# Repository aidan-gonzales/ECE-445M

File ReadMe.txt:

These files accompany "Introduction to Embedded Systems using the MSPM0+" 
Jonathan W. Valvano, ISBN: 978-1466468863, copyright (c) 2026

Most of the folders contain CCS projects. Folders that begin with the name RTOS_ are ECE445M lab starter projects

These folders do not contain CCS projects
  The documentation folder contains html descriptions created by Doxygen
  The datasheets folder contains data sheets for components used in this curriculum
  The RTOS_Labs_common folder contains shared files for the RTOS labs  
  The inc folder contains general shared files. 
  The SensorBoard_v8 folder contains design files for the sensor board
  The MotorBoard_v7 folder contains design files for the motor board

TExaSdisplay is a Windows application that implements a serial terminal, oscilloscope and logic analyzer.

Built 1/10/2026

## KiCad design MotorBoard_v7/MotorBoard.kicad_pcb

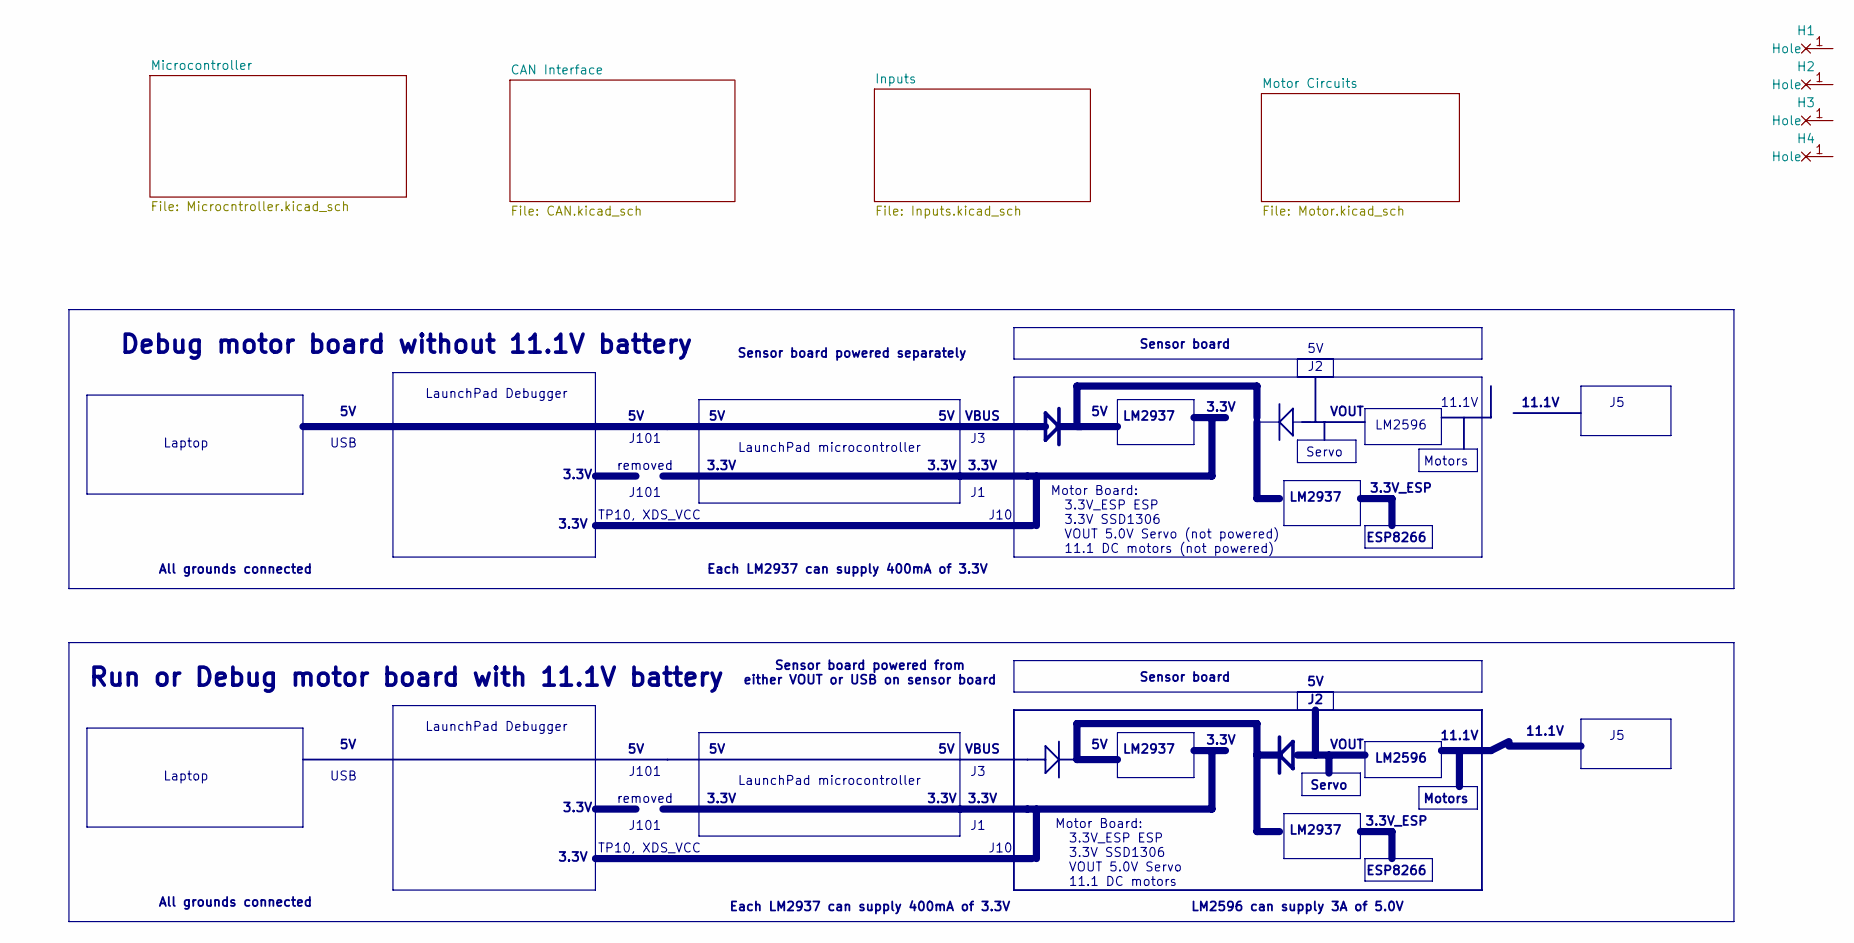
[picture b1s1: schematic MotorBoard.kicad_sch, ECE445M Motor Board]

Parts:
H1, H2, H3, H4: MountingHole_4_40

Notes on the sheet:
3.3V
Each LM2937 can supply 400mA of 3.3V
Motors
LaunchPad Debugger
3.3V_ESP
USB
Laptop
VOUT
Debug motor board without 11.1V battery
Sensor board
Motor Board: 3.3V_ESP ESP 3.3V SSD1306 VOUT 5.0V Servo 11.1 DC motors
Servo
LM2596 can supply 3A of 5.0V
VBUS
All grounds connected
ESP8266
LM2937
J10
LaunchPad microcontroller
removed
11.1V
Sensor board powered separately
LM2596
TP10, XDS_VCC
Run or Debug motor board with 11.1V battery
J101
Sensor board powered from either VOUT or USB on sensor board
Motor Board: 3.3V_ESP ESP 3.3V SSD1306 VOUT 5.0V Servo (not powered) 11.1 DC motors (not powered)

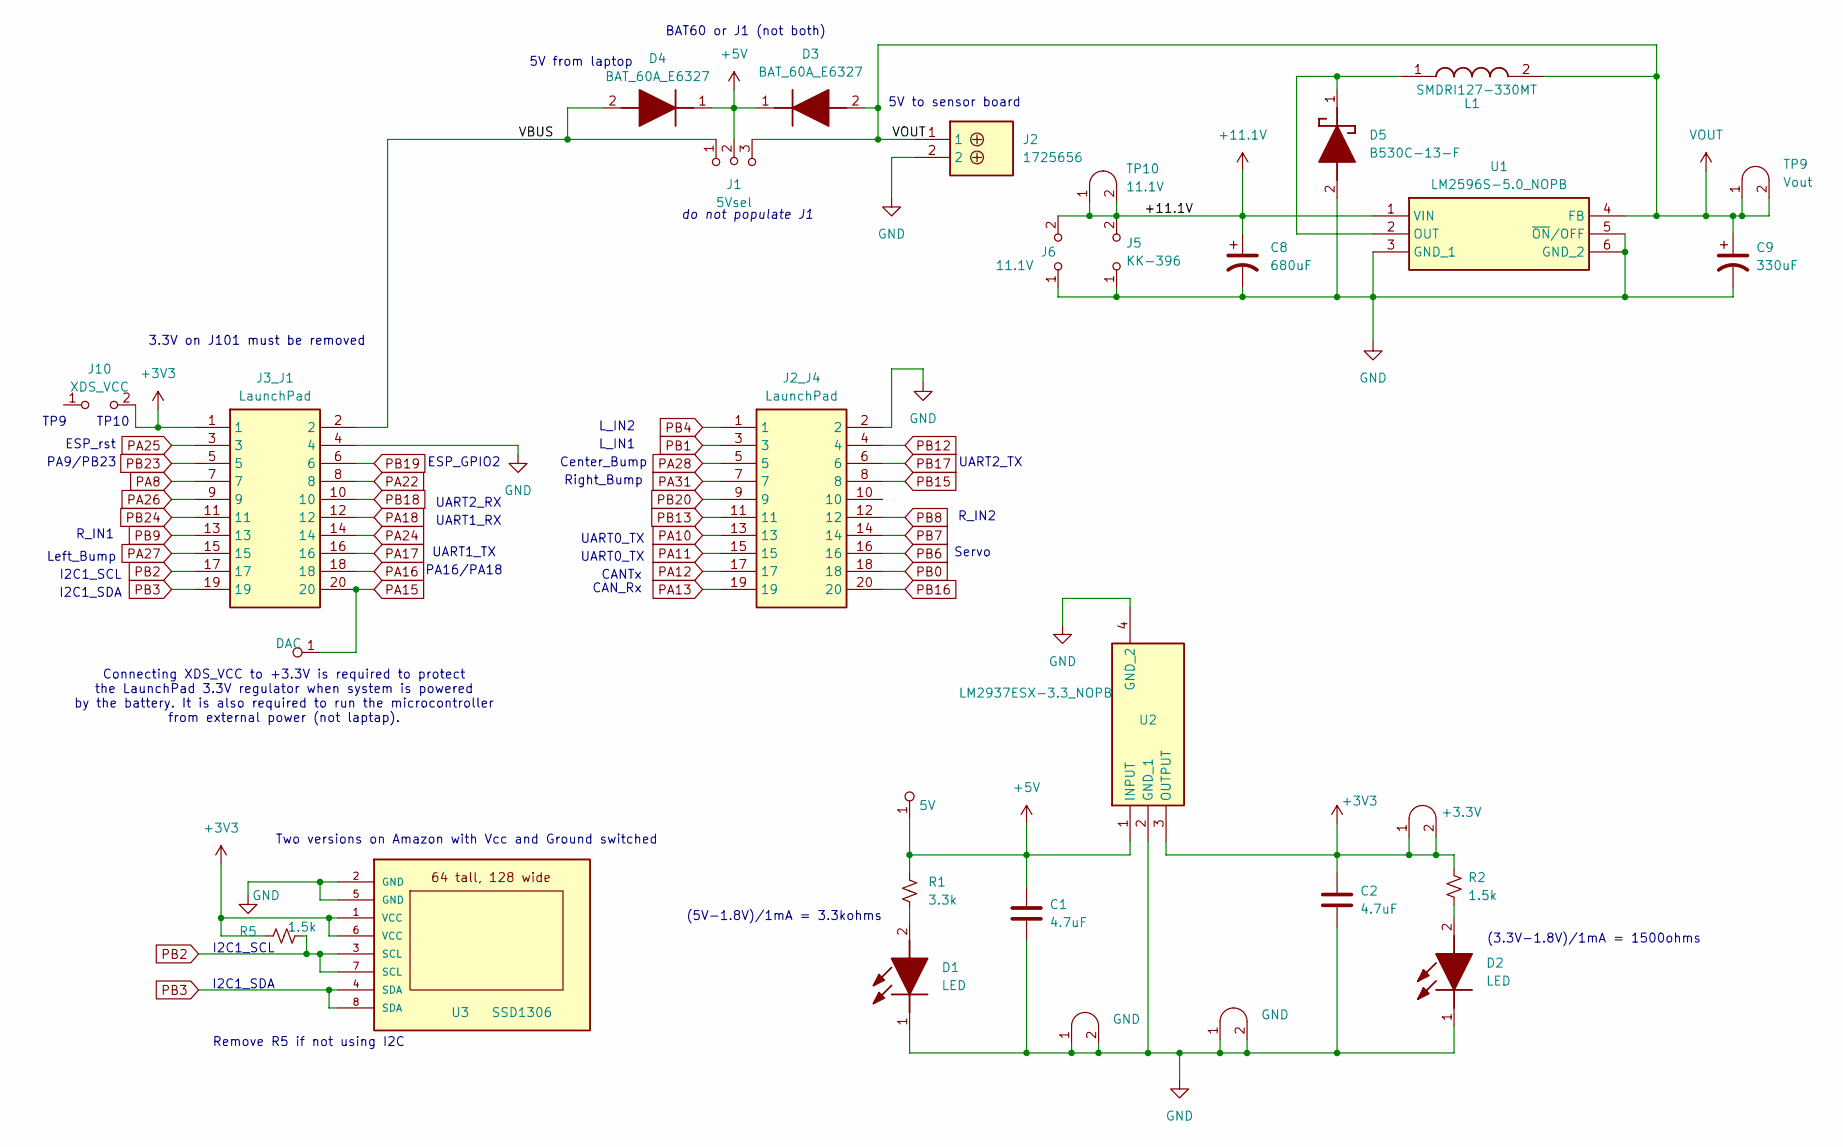
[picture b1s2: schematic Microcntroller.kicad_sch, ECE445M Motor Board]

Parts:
C1, C2: 4.7uF; C_0805_2012Metric; LCSC C5186689
C8: 680uF; CP_Elec_10x10.5; LCSC C2980172
C9: 330uF; CP_Elec_10x10.5; LCSC C5155335
D1, D2: LED; APT1608CGCK; Mouser Part Number 604-APTD1608LSECKJ3F
D3, D4: BAT_60A_E6327; SOD2513X110N; Mouser Part Number 726-BAT60AE6327
D5: B530C-13-F; DO-214AB; Mouser Part Number 621-B530C-13-F
J1: 5Vsel; PinHeader_1x03_P2.54mm_Vertical
J2: 1725656; Mouser Part Number 651-1725656
J2_J4, J3_J1: LaunchPad; Mouser Part Number 855-M20-8761042P
J5: KK-396; Molex_KK-396_A-41792-0002_1x02_P3.96mm_Horizontal
J6: 11.1V; PinHeader_1x02_P2.54mm_Vertical
J10: XDS_VCC; PinHeader_1x02_P2.54mm_Vertical
L1: SMDRI127-330MT; INDPM120120X800N; Mouser Part Number 851-CDRH127LDNP330MC
R1: 3.3k; R_0603_1608Metric; LCSC C340542
R2, R5: 1.5k; R_0603_1608Metric; LCSC C340542
TP1: DAC; Testpoint_1x1; Digikey 36-5000-ND, 36-5001-ND, 36-5002-ND , 36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
TP2: 5V; Testpoint_1x1; Digikey 36-5000-ND, 36-5001-ND, 36-5002-ND , 36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
TP3: +3.3V; Testpoint_1x02_P2.54mm; Digikey 36-5000-ND, 36-5001-ND, 36-5002-ND , 36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
TP9: Vout; Testpoint_1x02_P2.54mm
TP10: 11.1V; Testpoint_1x02_P2.54mm
TP11, TP16: GND; Testpoint_1x02_P2.54mm
U1: LM2596S-5.0_NOPB; KTT0005B; Mouser Part Number 926-LM2596S-5.0/NOPB
U2: LM2937ESX-3.3_NOPB; SOT230P700X180-4N; Mouser Part Number 926-LM2937IMP3.3NOPB
U3: SSD1306

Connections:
+3V3: C2.1, J3_J1.1, J10.2 (B), R2.1, R5.1, TP3.1 (A), TP3.2 (B), U2.3 (OUTPUT), U3.1 (VCC), U3.6 (VCC); also elsewhere on the board
+5V: C1.1, D3.1 (K), D4.1 (K), J1.2 (B), R1.1, TP2.1 (A), U2.1 (INPUT); also elsewhere on the board
+11.1V: C8.1, J5.2 (B), J6.2 (B), TP10.1 (A), TP10.2 (B), U1.1 (VIN); also elsewhere on the board
/Microcontroller/VBUS: D4.2 (A), J1.1 (A), J3_J1.2
GND: C1.2, C2.2, C8.2, C9.2, D1.1 (K), D2.1 (K), D5.2 (A), J2.2, J2_J4.2, J3_J1.4, J5.1 (A), J6.1 (A), TP11.1 (A), TP11.2 (B), TP16.1 (A), TP16.2 (B), U1.3 (GND_1), U1.5 (~ON/OFF), U1.6 (GND_2), U2.2 (GND_1), U2.4 (GND_2), U3.2 (GND), U3.5 (GND); also elsewhere on the board
unnamed: D1.2 (A), R1.2
unnamed: D2.2 (A), R2.2
unnamed: D5.1 (K), L1.1, U1.2 (OUT)
PA8: J3_J1.7
PA10: J2_J4.13
PA11: J2_J4.15
PA12: J2_J4.17; also elsewhere on the board
PA13: J2_J4.19; also elsewhere on the board
PA15: J3_J1.20, TP1.1 (A)
PA16: J3_J1.18
PA17: J3_J1.16
PA18: J3_J1.12
PA22: J3_J1.8
PA24: J3_J1.14
PA25: J3_J1.3; also elsewhere on the board
PA26: J3_J1.9
PA27: J3_J1.15; also elsewhere on the board
PA28: J2_J4.5; also elsewhere on the board
PA31: J2_J4.7; also elsewhere on the board
PB0: J2_J4.18
PB1: J2_J4.3; also elsewhere on the board
PB2: J3_J1.17, R5.2, U3.3 (SCL), U3.7 (SCL)
PB3: J3_J1.19, U3.4 (SDA), U3.8 (SDA)
PB4: J2_J4.1; also elsewhere on the board
PB6: J2_J4.16; also elsewhere on the board
PB7: J2_J4.14
PB8: J2_J4.12; also elsewhere on the board
PB9: J3_J1.13; also elsewhere on the board
PB12: J2_J4.4
PB13: J2_J4.11
PB15: J2_J4.8
PB16: J2_J4.20
PB17: J2_J4.6; also elsewhere on the board
PB18: J3_J1.10; also elsewhere on the board
PB19: J3_J1.6; also elsewhere on the board
PB20: J2_J4.9
PB23: J3_J1.5
PB24: J3_J1.11
VOUT: C9.1, D3.2 (A), J1.3 (C), J2.1, L1.2, TP9.1 (A), TP9.2 (B), U1.4 (FB); also elsewhere on the board

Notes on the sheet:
TP10
UART0_TX
UART1_RX
(5V-1.8V)/1mA = 3.3kohms
(3.3V-1.8V)/1mA = 1500ohms
Left_Bump
5V from laptop
ESP_GPIO2
UART2_RX
CANTx
UART1_TX
Right_Bump
3.3V on J101 must be removed
L_IN1
Servo
Center_Bump
I2C1_SDA
PA16/PA18
BAT60 or J1 (not both)
Remove R5 if not using I2C
TP9
do not populate J1
UART2_TX
R_IN2
PA9/PB23
I2C1_SCL
5V to sensor board
R_IN1
CAN_Rx
ESP_rst
Two versions on Amazon with Vcc and Ground switched
Connecting XDS_VCC to +3.3V is required to protect the LaunchPad 3.3V regulator when system is powered by the battery. It is also required to run the microcontroller from external power (not laptap).
L_IN2

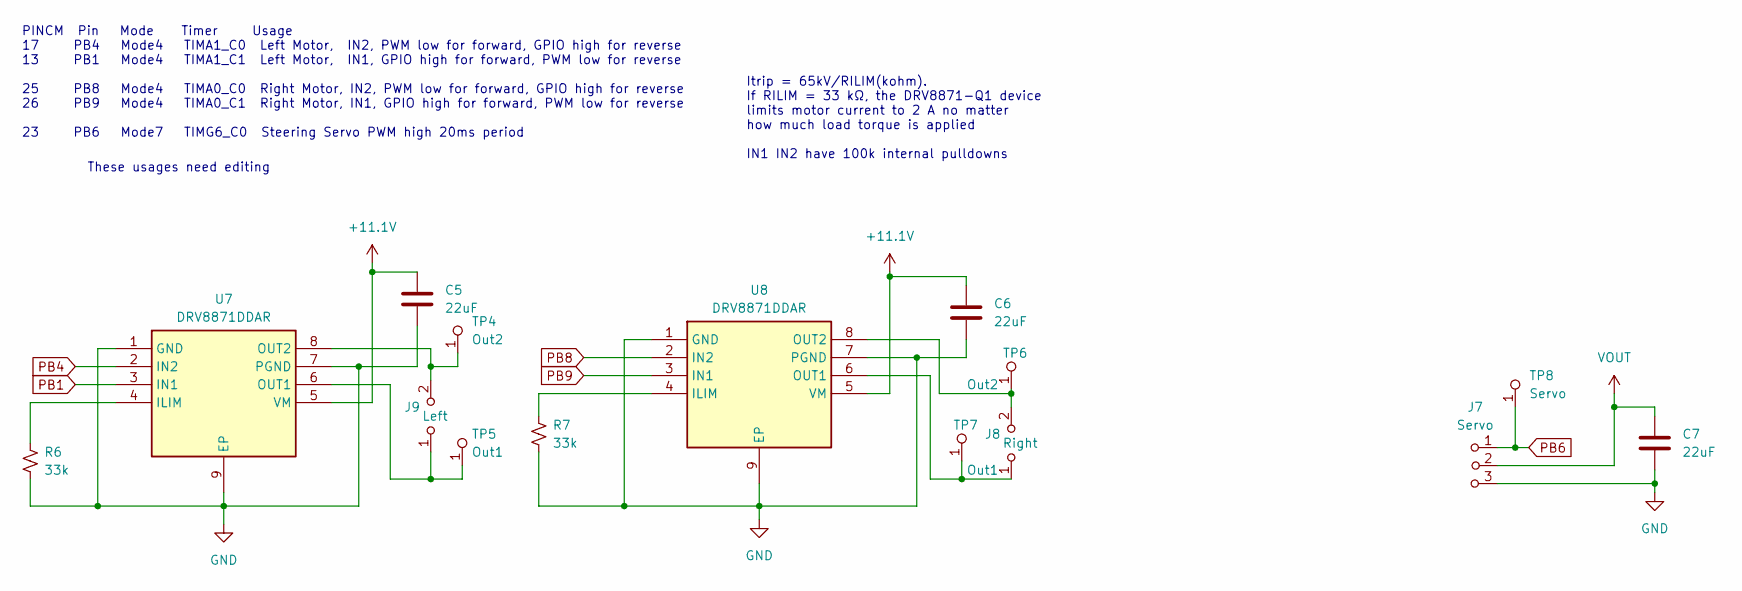
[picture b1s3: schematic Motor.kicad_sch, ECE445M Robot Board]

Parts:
C5, C6, C7: 22uF; C_0805_2012Metric; LCSC C5186689
J7: Servo; PinHeader_1x03_P2.54mm_Vertical
J8: Right; Molex_KK-396_5273-02A_1x02_P3.96mm_Vertical
J9: Left; Molex_KK-396_5273-02A_1x02_P3.96mm_Vertical
R6, R7: 33k; R_0603_1608Metric; LCSC C340542
TP4, TP6: Out2; Testpoint_1x1; Digikey 36-5000-ND, 36-5001-ND, 36-5002-ND , 36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
TP5, TP7: Out1; Testpoint_1x1; Digikey 36-5000-ND, 36-5001-ND, 36-5002-ND , 36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
TP8: Servo; Testpoint_1x1; Digikey 36-5000-ND, 36-5001-ND, 36-5002-ND , 36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
U7, U8: DRV8871DDAR; SOIC127P600X170-9N; Mouser Part Number 595-DRV8871DDAR

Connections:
+11.1V: C5.1, C6.1, U7.5 (VM), U8.5 (VM); also elsewhere on the board
GND: C5.2, C6.2, C7.2, J7.3 (C), R6.2, R7.2, U7.1 (GND), U7.7 (PGND), U7.9 (EP), U8.1 (GND), U8.7 (PGND), U8.9 (EP); also elsewhere on the board
unnamed: J8.1 (A), TP7.1 (A), U8.6 (OUT1)
unnamed: J8.2 (B), TP6.1 (A), U8.8 (OUT2)
unnamed: J9.1 (A), TP5.1 (A), U7.6 (OUT1)
unnamed: J9.2 (B), TP4.1 (A), U7.8 (OUT2)
unnamed: R6.1, U7.4 (ILIM)
unnamed: R7.1, U8.4 (ILIM)
PB1: U7.3 (IN1); also elsewhere on the board
PB4: U7.2 (IN2); also elsewhere on the board
PB6: J7.1 (A), TP8.1 (A); also elsewhere on the board
PB8: U8.2 (IN2); also elsewhere on the board
PB9: U8.3 (IN1); also elsewhere on the board
VOUT: C7.1, J7.2 (B); also elsewhere on the board

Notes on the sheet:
PINCM Pin Mode Timer Usage 17 PB4 Mode4 TIMA1_C0 Left Motor, IN2, PWM low for forward, GPIO high for reverse 13 PB1 Mode4 TIMA1_C1 Left Motor, IN1, GPIO high for forward, PWM low for reverse 25 PB8 Mode4 TIMA0_C0 Right Motor, IN2, PWM low for forward, GPIO high for reverse 26 PB9 Mode4 TIMA0_C1 Rig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
Itrip = 65kV/RILIM(kohm). If RILIM = 33 kΩ, the DRV8871-Q1 device limits motor current to 2 A no matter how much load torque is applied IN1 IN2 have 100k internal pulldowns
These usages need editing

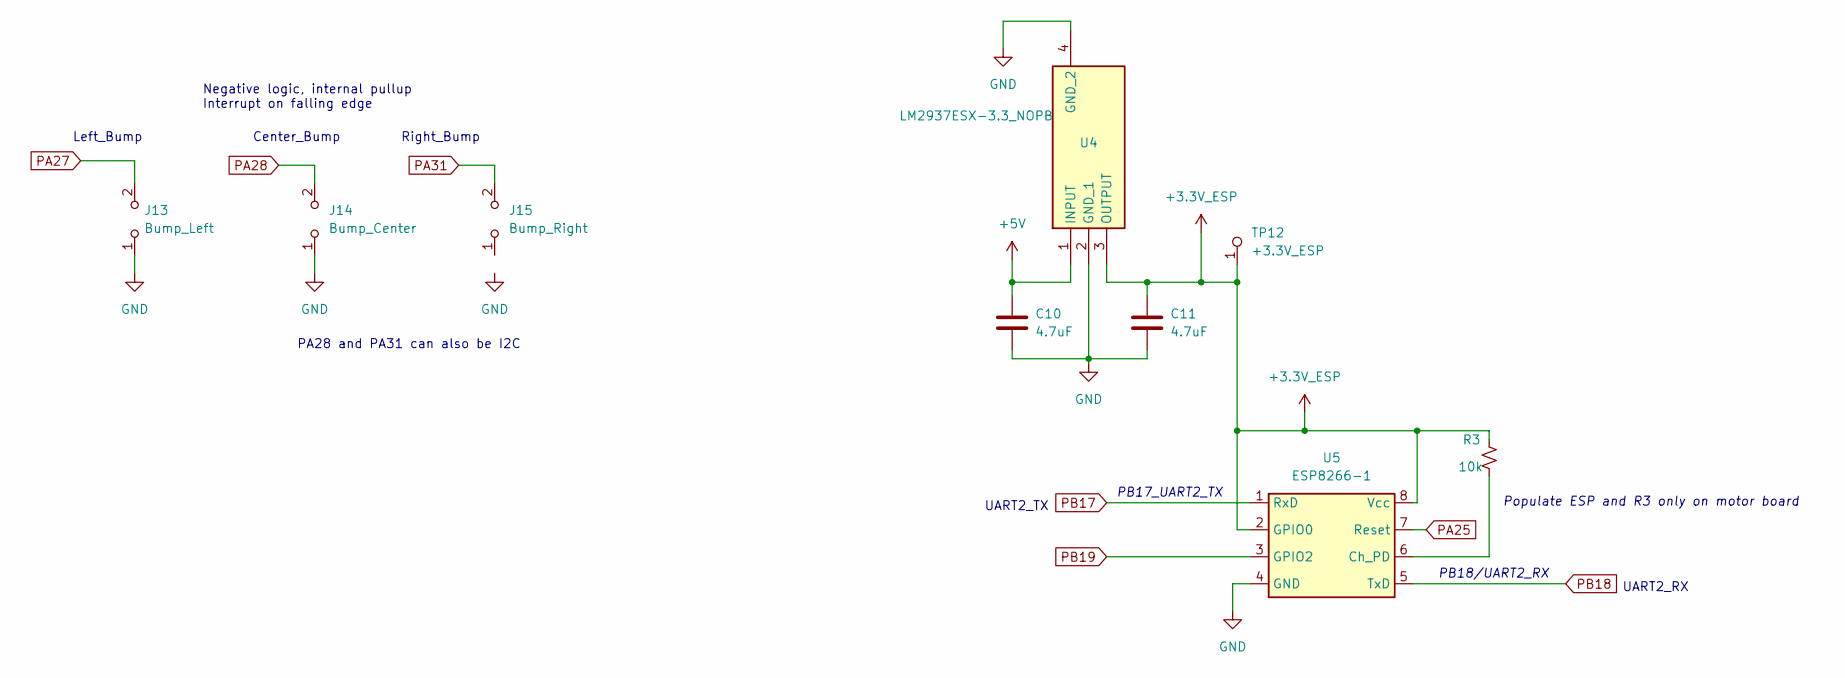
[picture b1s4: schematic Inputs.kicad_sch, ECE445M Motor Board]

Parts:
C10, C11: 4.7uF; C_0805_2012Metric; LCSC C5186689
J13: Bump_Left; PinHeader_1x02_P2.54mm_Vertical
J14: Bump_Center; PinHeader_1x02_P2.54mm_Vertical
J15: Bump_Right; PinHeader_1x02_P2.54mm_Vertical
R3: 10k; R_0603_1608Metric
TP12: +3.3V_ESP; Testpoint_1x1; Digikey 36-5000-ND, 36-5001-ND, 36-5002-ND , 36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
U4: LM2937ESX-3.3_NOPB; SOT230P700X180-4N; Mouser Part Number 926-LM2937IMP3.3NOPB
U5: ESP8266-1; PinHeader_2x04_P2.54mm_Vertical

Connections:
+3.3V_ESP: C11.1, R3.1, TP12.1 (A), U4.3 (OUTPUT), U5.2 (GPIO0), U5.8 (Vcc)
+5V: C10.1, U4.1 (INPUT); also elsewhere on the board
GND: C10.2, C11.2, J13.1 (A), J14.1 (A), U4.2 (GND_1), U4.4 (GND_2), U5.4 (GND); also elsewhere on the board
unnamed: R3.2, U5.6 (Ch_PD)
PA25: U5.7 (Reset); also elsewhere on the board
PA27: J13.2 (B); also elsewhere on the board
PA28: J14.2 (B); also elsewhere on the board
PA31: J15.2 (B); also elsewhere on the board
PB17: U5.1 (RxD); also elsewhere on the board
PB18: U5.5 (TxD); also elsewhere on the board
PB19: U5.3 (GPIO2); also elsewhere on the board

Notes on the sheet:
Center_Bump
Populate ESP and R3 only on motor board
PB17_UART2_TX
PB18/UART2_RX
PA28 and PA31 can also be I2C
UART2_RX
Negative logic, internal pullup Interrupt on falling edge
Left_Bump
UART2_TX
Right_Bump

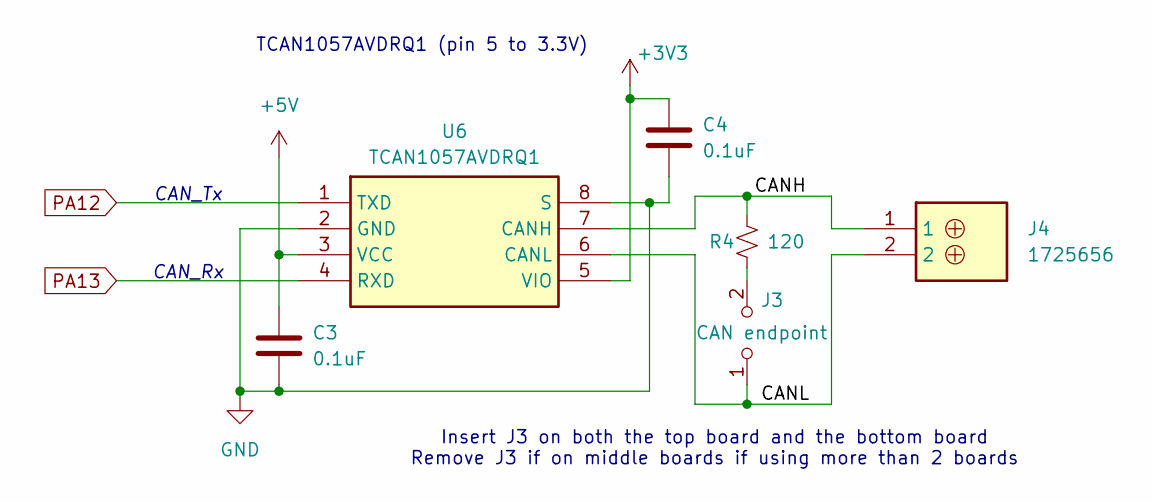
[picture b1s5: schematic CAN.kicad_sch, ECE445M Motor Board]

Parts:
C3, C4: 0.1uF; C_0603_1608Metric; LCSC C5186689
J3: CAN endpoint; PinHeader_1x02_P2.54mm_Vertical
J4: 1725656; Mouser Part Number 651-1725656
R4: 120; R_0603_1608Metric; LCSC C340542
U6: TCAN1057AVDRQ1; SOIC127P600X175-8N; Mouser Part Number 595-TCAN1057AVDRQ1

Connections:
+3V3: C4.1, U6.5 (VIO); also elsewhere on the board
+5V: C3.1, U6.3 (VCC); also elsewhere on the board
/CAN Interface/CANH: J4.1, R4.1, U6.7 (CANH)
/CAN Interface/CANL: J3.1 (A), J4.2, U6.6 (CANL)
GND: C3.2, C4.2, U6.2 (GND), U6.8 (S); also elsewhere on the board
unnamed: J3.2 (B), R4.2
PA12: U6.1 (TXD); also elsewhere on the board
PA13: U6.4 (RXD); also elsewhere on the board

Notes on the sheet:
Insert J3 on both the top board and the bottom board Remove J3 if on middle boards if using more than 2 boards
CAN_Tx
TCAN1057AVDRQ1 (pin 5 to 3.3V)
CAN_Rx

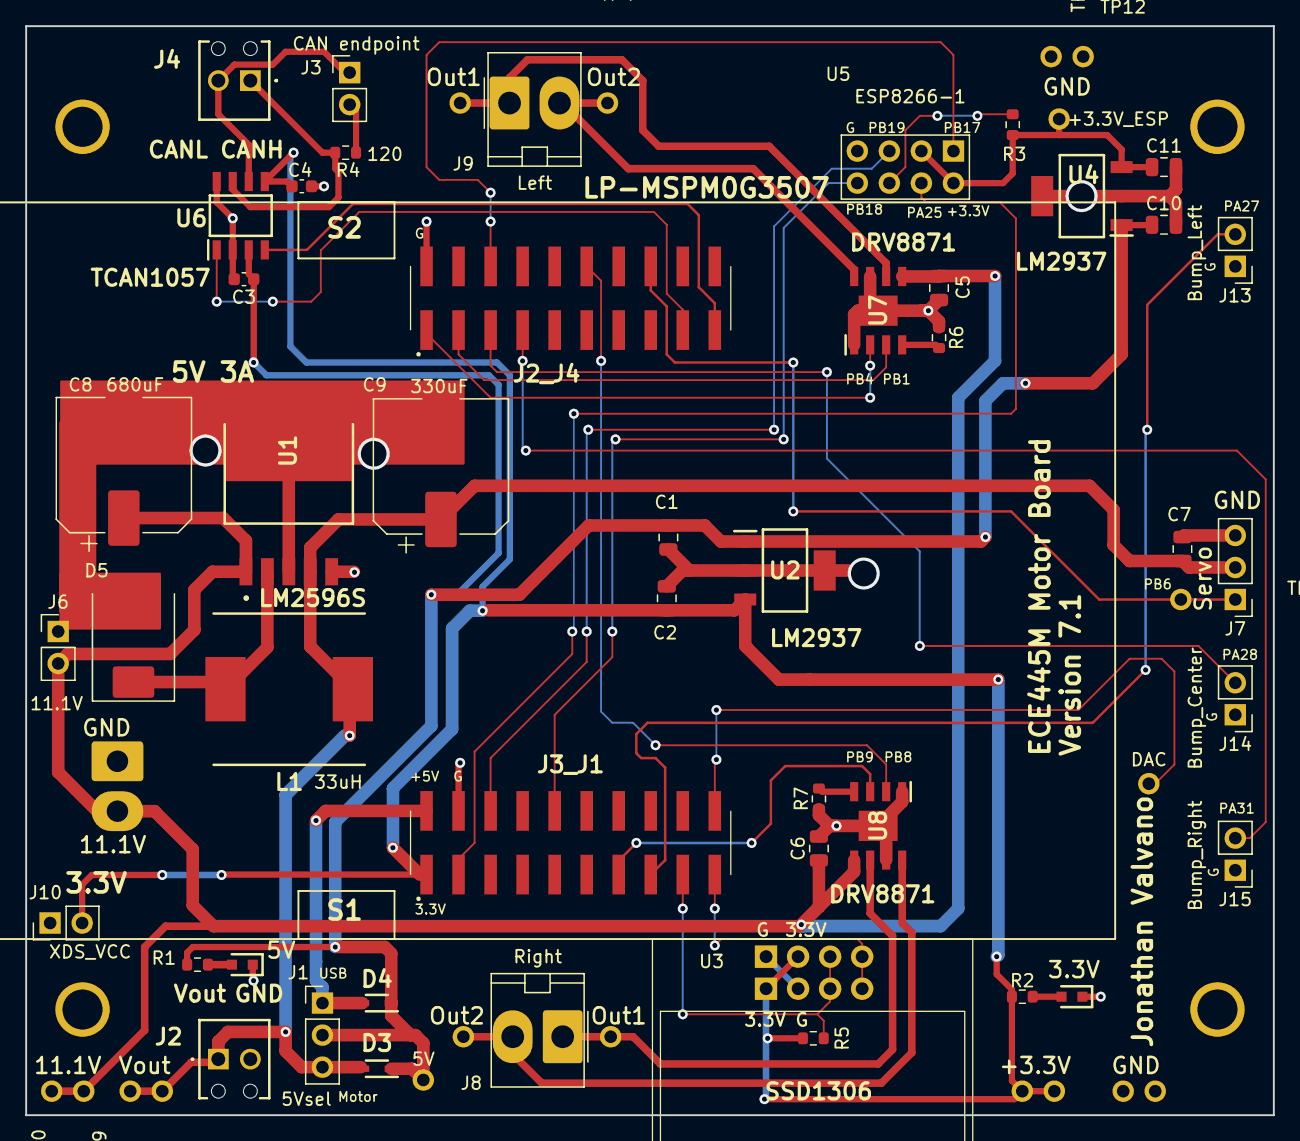
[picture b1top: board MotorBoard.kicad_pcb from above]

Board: 2 copper layers, 98.9 x 86.4 mm, 64 parts (1 on the bottom side), 37 nets.

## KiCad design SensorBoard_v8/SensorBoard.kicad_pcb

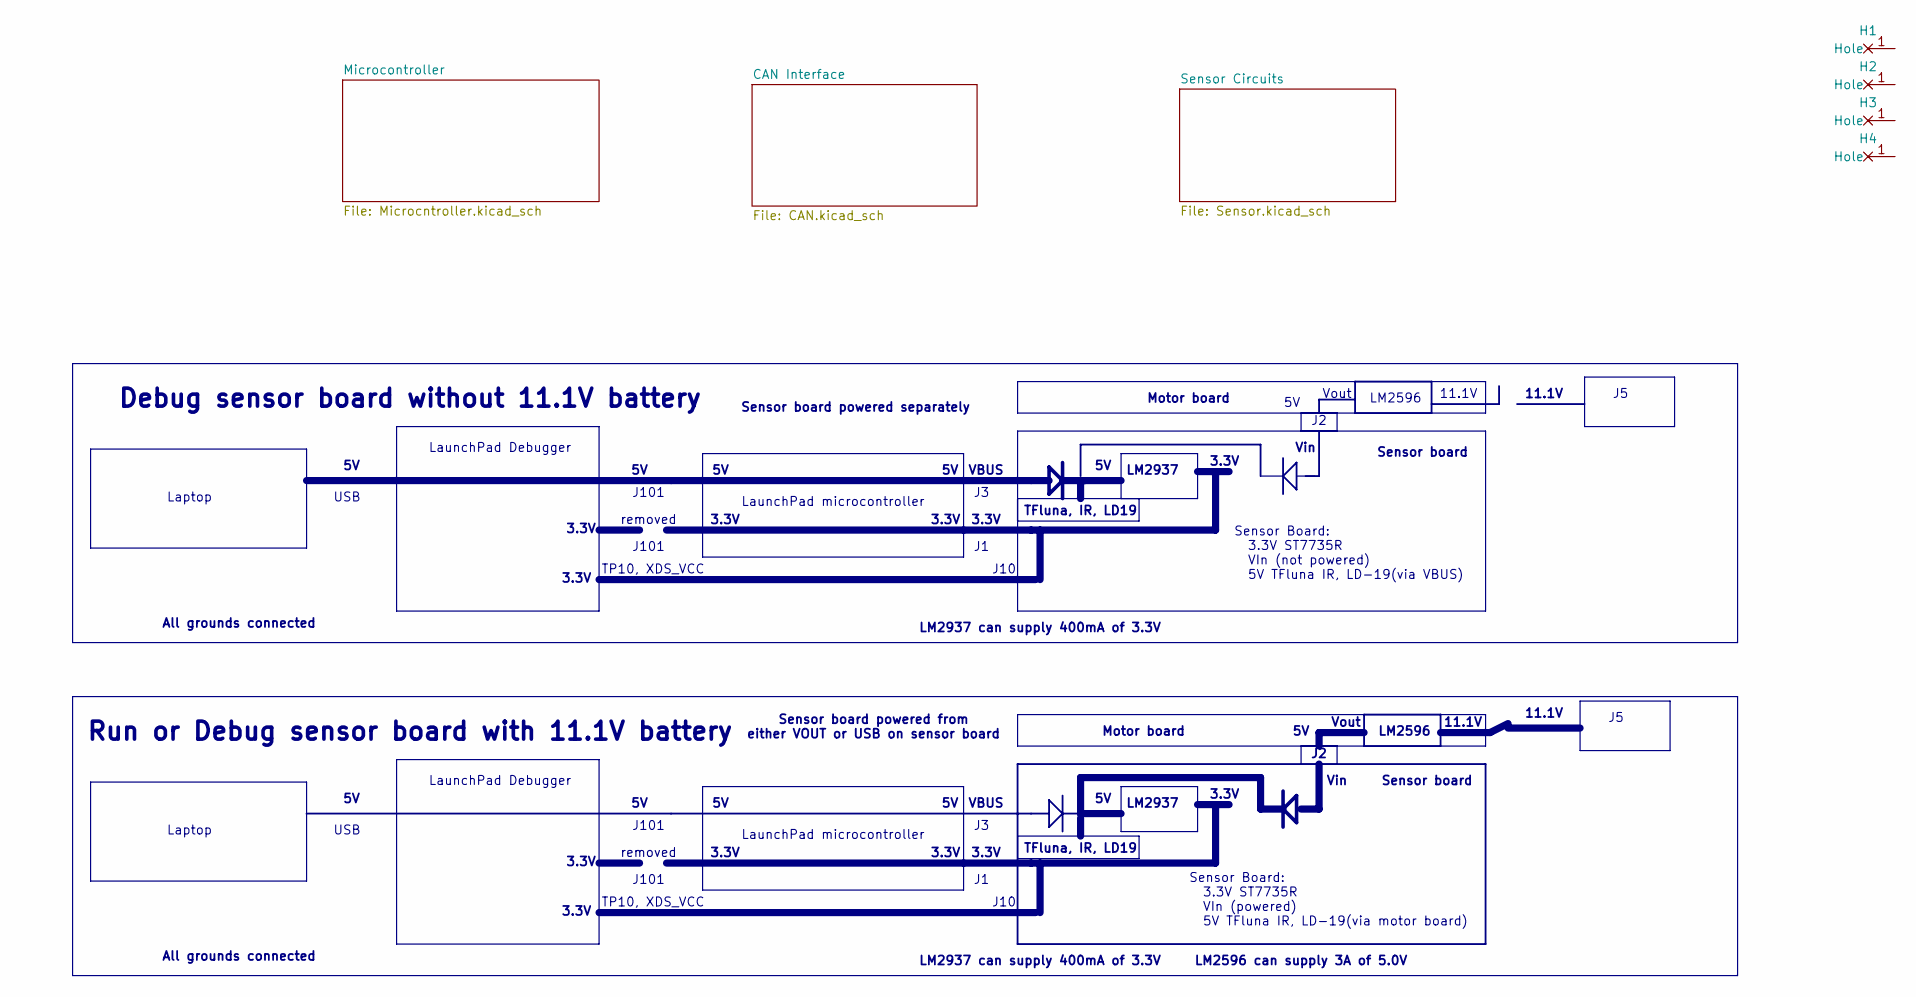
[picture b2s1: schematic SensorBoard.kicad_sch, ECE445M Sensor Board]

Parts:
H1, H2, H3, H4: MountingHole_4_40

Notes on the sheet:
LM2596
LM2937
11.1V
USB
J10
Sensor board powered from either VOUT or USB on sensor board
LaunchPad microcontroller
3.3V
Sensor board powered separately
TFluna, IR, LD19
LaunchPad Debugger
All grounds connected
J101
Run or Debug sensor board with 11.1V battery
removed
Sensor board
LM2937 can supply 400mA of 3.3V
VBUS
Motor board
Vout
Vin
LM2596 can supply 3A of 5.0V
TP10, XDS_VCC
Laptop
Sensor Board: 3.3V ST7735R VIn (powered) 5V TFluna IR, LD-19(via motor board)
Debug sensor board without 11.1V battery
Sensor Board: 3.3V ST7735R VIn (not powered) 5V TFluna IR, LD-19(via VBUS)

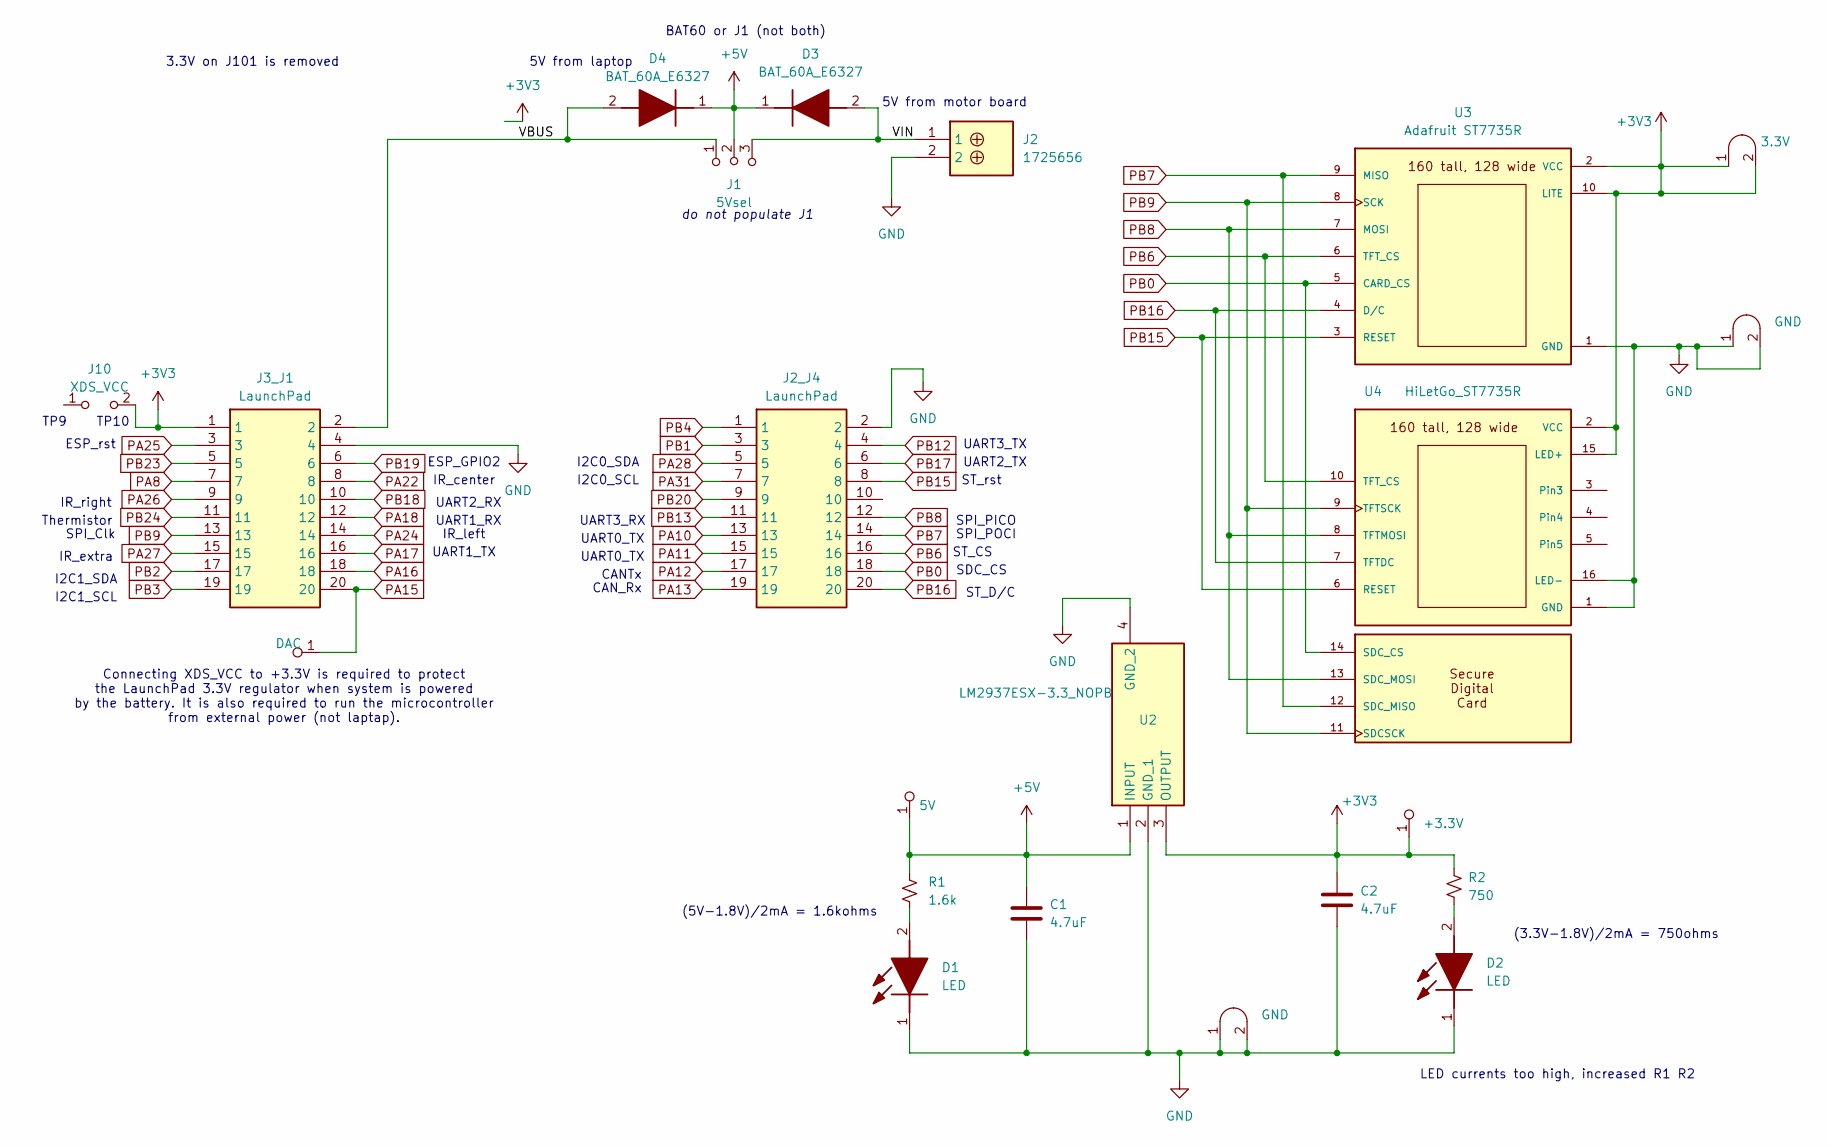
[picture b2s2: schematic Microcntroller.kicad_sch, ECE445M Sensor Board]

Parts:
C1, C2: 4.7uF; C_0805_2012Metric; LCSC C5186689
D1, D2: LED; APT1608CGCK; Mouser Part Number 604-APTD1608LSECKJ3F
D3, D4: BAT_60A_E6327; SOD2513X110N; Mouser Part Number 726-BAT60AE6327
J1: 5Vsel; PinHeader_1x03_P2.54mm_Vertical
J2: 1725656; Mouser Part Number 651-1725656
J2_J4, J3_J1: LaunchPad; Mouser Part Number 855-M20-8761042P
J10: XDS_VCC; PinHeader_1x02_P2.54mm_Vertical
R1: 1.6k; R_0603_1608Metric; LCSC C340542
R2: 750; R_0603_1608Metric; LCSC C340542
TP1: DAC; Testpoint_1x1; Digikey 36-5000-ND, 36-5001-ND, 36-5002-ND , 36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
TP2: 5V; Testpoint_1x1; Digikey 36-5000-ND, 36-5001-ND, 36-5002-ND , 36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
TP3: +3.3V; Testpoint_1x1; Digikey 36-5000-ND, 36-5001-ND, 36-5002-ND , 36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
TP4: 3.3V; Testpoint_1x02_P2.54mm
TP5, TP16: GND; Testpoint_1x02_P2.54mm
U2: LM2937ESX-3.3_NOPB; SOT230P700X180-4N; Mouser Part Number 926-LM2937IMP3.3NOPB
U3: Adafruit ST7735R; adafruit_st7735r
U4: HiLetGo_ST7735R; hiletgo_st7735r2

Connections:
+3V3: C2.1, J3_J1.1, J10.2 (B), R2.1, TP3.1 (A), TP4.1 (A), TP4.2 (B), U2.3 (OUTPUT), U3.2 (VCC), U3.10 (LITE), U4.2 (VCC), U4.15 (LED+); also elsewhere on the board
+5V: C1.1, D3.1 (K), D4.1 (K), J1.2 (B), R1.1, TP2.1 (A), U2.1 (INPUT); also elsewhere on the board
/Microcontroller/VBUS: D4.2 (A), J1.1 (A), J3_J1.2
/Microcontroller/VIN: D3.2 (A), J1.3 (C), J2.1
GND: C1.2, C2.2, D1.1 (K), D2.1 (K), J2.2, J2_J4.2, J3_J1.4, TP5.1 (A), TP5.2 (B), TP16.1 (A), TP16.2 (B), U2.2 (GND_1), U2.4 (GND_2), U3.1 (GND), U4.1 (GND), U4.16 (LED-); also elsewhere on the board
unnamed: D1.2 (A), R1.2
unnamed: D2.2 (A), R2.2
PA8: J3_J1.7
PA10: J2_J4.13
PA11: J2_J4.15
PA12: J2_J4.17; also elsewhere on the board
PA13: J2_J4.19; also elsewhere on the board
PA15: J3_J1.20, TP1.1 (A)
PA16: J3_J1.18
PA17: J3_J1.16; also elsewhere on the board
PA18: J3_J1.12; also elsewhere on the board
PA22: J3_J1.8; also elsewhere on the board
PA24: J3_J1.14; also elsewhere on the board
PA25: J3_J1.3; also elsewhere on the board
PA26: J3_J1.9; also elsewhere on the board
PA27: J3_J1.15; also elsewhere on the board
PA28: J2_J4.5; also elsewhere on the board
PA31: J2_J4.7
PB0: J2_J4.18, U3.5 (CARD_CS), U4.14 (SDC_CS)
PB1: J2_J4.3
PB2: J3_J1.17
PB3: J3_J1.19
PB4: J2_J4.1
PB6: J2_J4.16, U3.6 (TFT_CS), U4.10 (TFT_CS)
PB7: J2_J4.14, U3.9 (MISO), U4.12 (SDC_MISO)
PB8: J2_J4.12, U3.7 (MOSI), U4.8 (TFTMOSI), U4.13 (SDC_MOSI)
PB9: J3_J1.13, U3.8 (SCK), U4.9 (TFTSCK), U4.11 (SDCSCK)
PB12: J2_J4.4; also elsewhere on the board
PB13: J2_J4.11; also elsewhere on the board
PB15: J2_J4.8, U3.3 (RESET), U4.6 (RESET)
PB16: J2_J4.20, U3.4 (D/C), U4.7 (TFTDC)
PB17: J2_J4.6; also elsewhere on the board
PB18: J3_J1.10; also elsewhere on the board
PB19: J3_J1.6; also elsewhere on the board
PB20: J2_J4.9
PB23: J3_J1.5
PB24: J3_J1.11

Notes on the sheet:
TP10
UART2_TX
UART0_TX
IR_left
UART1_RX
I2C0_SDA
IR_extra
5V from laptop
IR_center
ESP_GPIO2
LED currents too high, increased R1 R2
UART2_RX
CANTx
UART1_TX
(5V-1.8V)/2mA = 1.6kohms
UART3_TX
(3.3V-1.8V)/2mA = 750ohms
3.3V on J101 is removed
ST_rst
I2C0_SCL
ST_CS
BAT60 or J1 (not both)
TP9
SPI_POCI
UART3_RX
Thermistor
do not populate J1
SDC_CS
IR_right
I2C1_SDA
ST_D/C
5V from motor board
SPI_Clk
CAN_Rx
ESP_rst
I2C1_SCL
Connecting XDS_VCC to +3.3V is required to protect the LaunchPad 3.3V regulator when system is powered by the battery. It is also required to run the microcontroller from external power (not laptap).
SPI_PICO
